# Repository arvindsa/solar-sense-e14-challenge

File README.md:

# SolarSense: Smart Solar Panel Monitoring System

A comprehensive IoT system for real-time solar panel soiling detection using multi-sensor fusion and edge AI. This project monitors three solar panels -one kept clean as a reference baseline to quantify soiling-induced efficiency losses in real time.

**Important: There is an issue with charging circuit. So do not replicate this project unless you know electronics well.**

## Project Overview

SolarSense uses a clean reference panel to cancel out weather effects completely (both panels see the same sky), leaving only soiling-induced losses measurable. The system combines:

- **Hardware**: Custom STM32L476 sensor board with CAN telemetry
- **Gateway**: Arduino UNO Q with dual STM32U585 (bare-metal HAL) and Linux bridge
- **Dashboard**: LabVIEW-based live visualization
- **AI**: Edge Impulse model for clean/alert/soiled classification

**Current Status**: Phase 1 (data collection and live dashboard) complete. Full pipeline implemented but pending end-to-end hardware validation.

Write-up: https://community.element14.com/challenges-projects/design-challenges/on-the-line/b/projects/posts/solarsense---edge-ai-for-optimal-cleaning-of-solar-panels

## Repository Structure

```
firmware/
├── solar-sense-stm32l476/       # Main sensor board (STM32L476RGT6)
├── arduinoq-stm32u585/          # Gateway STM controller (bare-metal HAL)
│   └── bridge/                  # CAN frame bridging logic
└── arduinoq-linux/              # Gateway Linux side (Python bridge)

labview/                         # Dashboard VIs for Window
hardware/                        # PCB schematics and production files
```

Do not use the Python file inside the labview folder. It's only for testing purpose

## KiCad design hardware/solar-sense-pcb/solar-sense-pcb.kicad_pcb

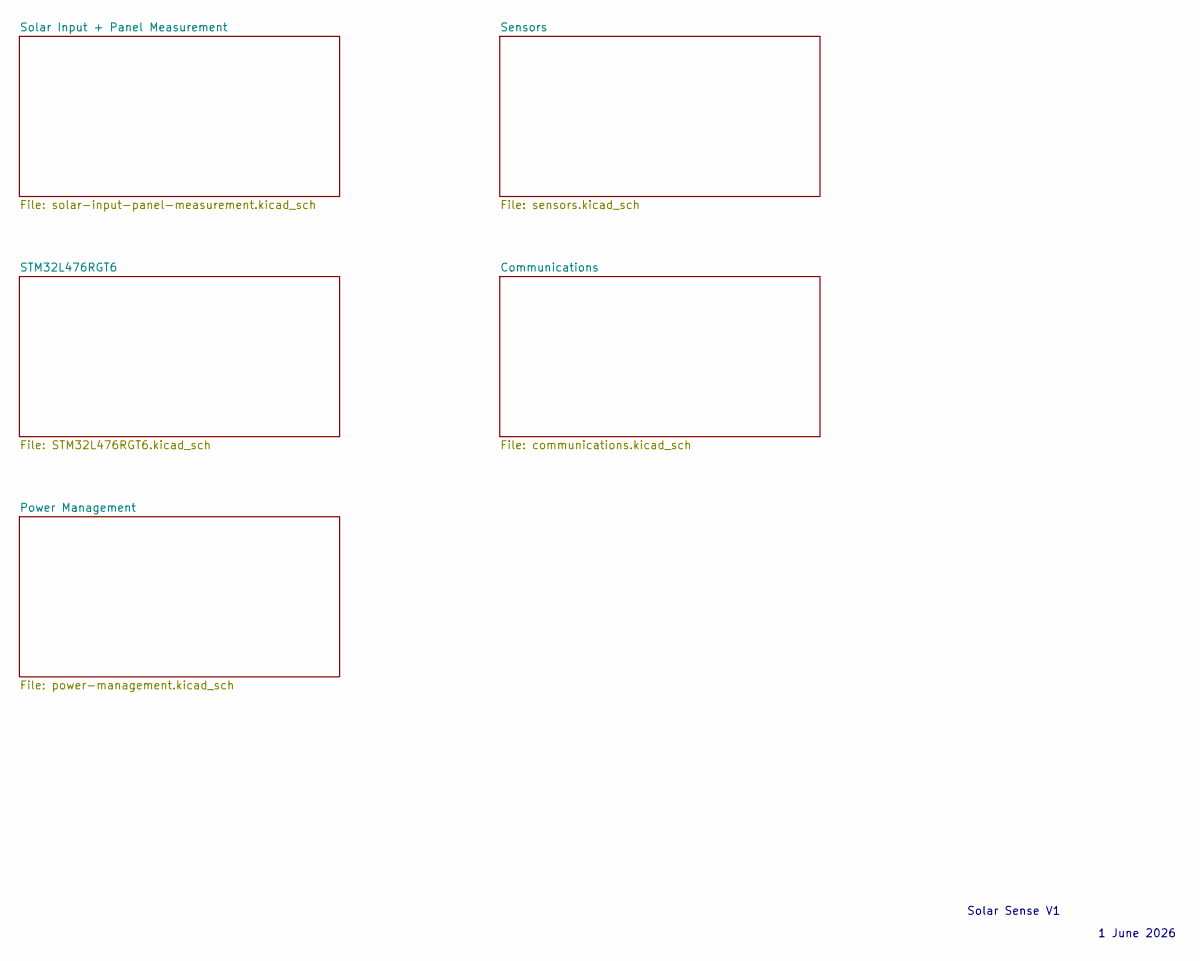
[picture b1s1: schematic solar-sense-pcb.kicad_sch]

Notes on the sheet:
1 June 2026
Solar Sense V1

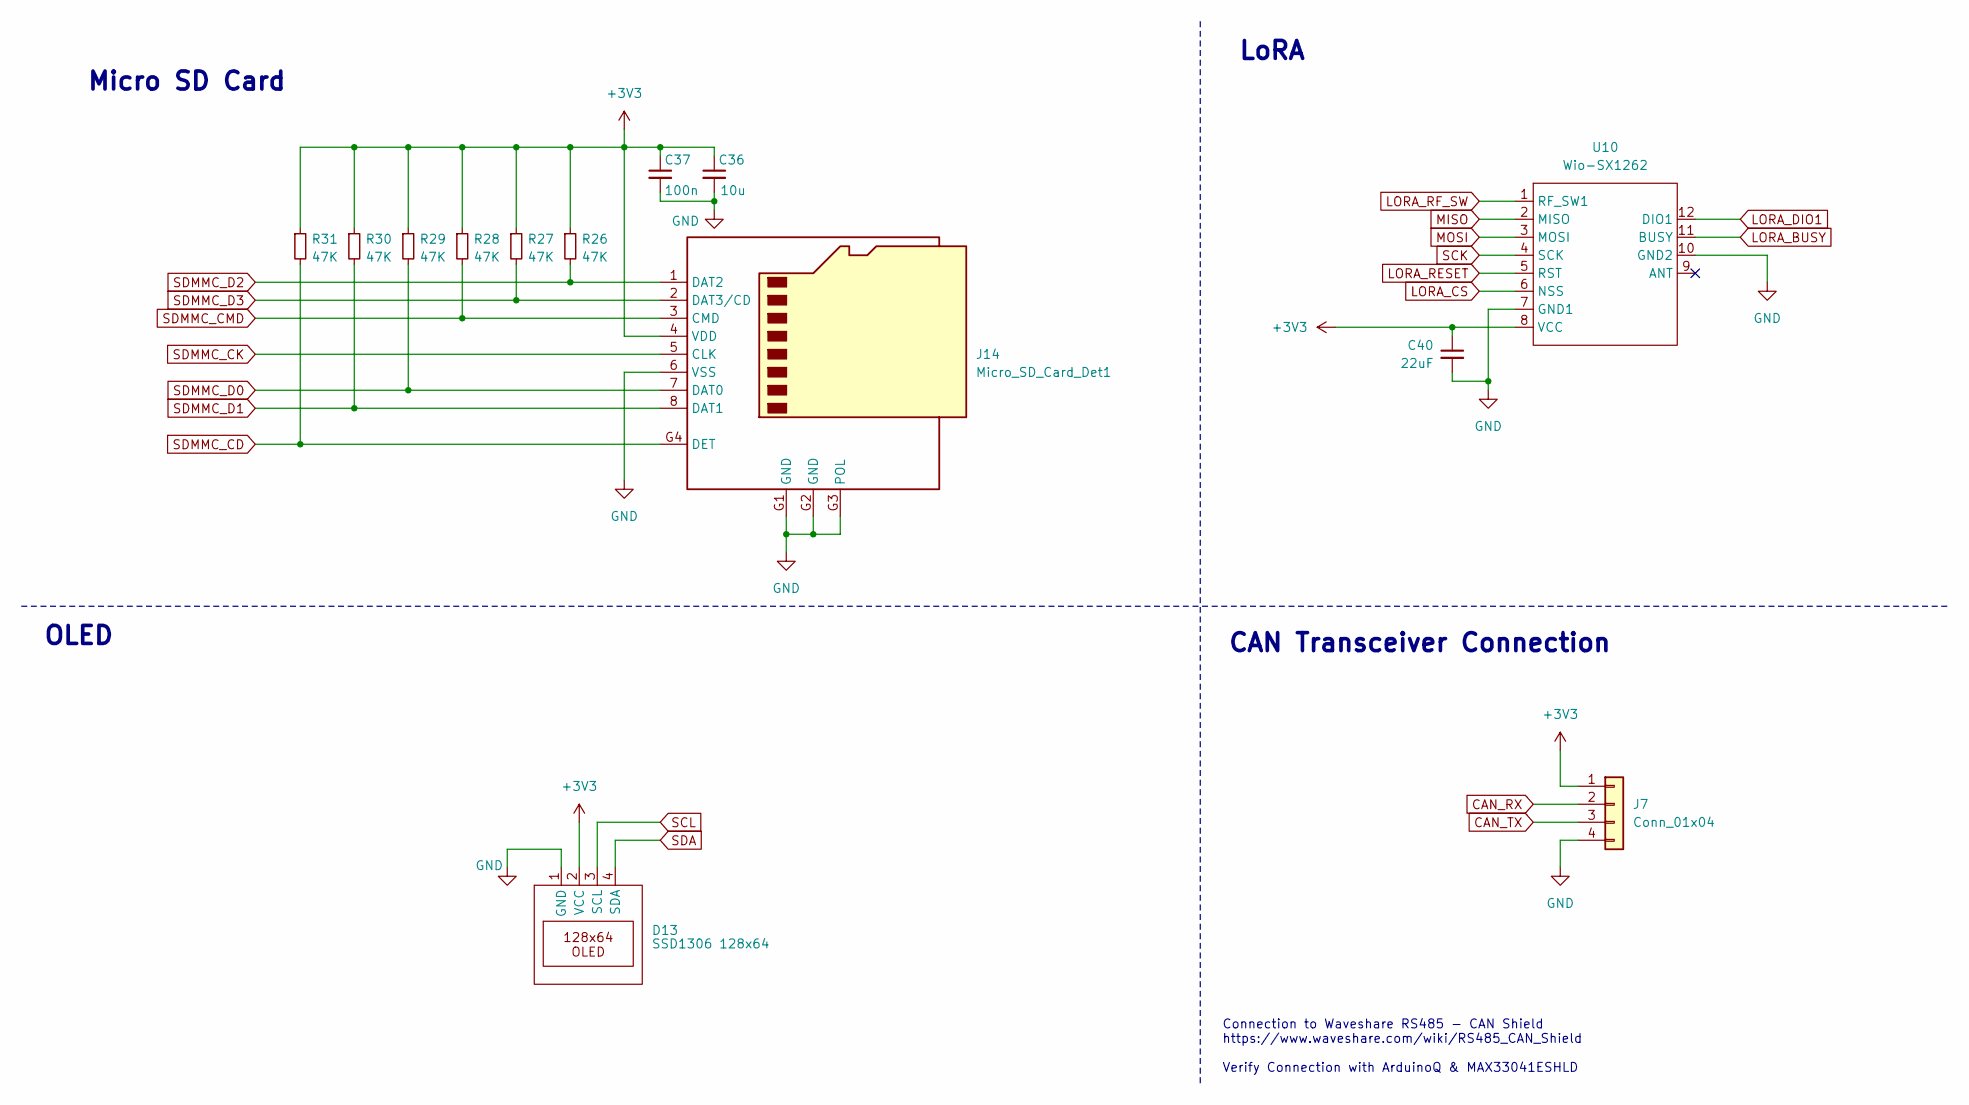
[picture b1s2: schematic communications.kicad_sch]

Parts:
C36: 10u; C_0603_1608Metric_Pad1.08x0.95mm_HandSolder
C37: 100n; C_0603_1608Metric_Pad1.08x0.95mm_HandSolder
C40: 22uF; C_0603_1608Metric
D13: SSD1306 128x64; JST_XH_B4B-XH-A_1x04_P2.50mm_Vertical
J7: Conn_01x04; JST_XH_B4B-XH-A_1x04_P2.50mm_Vertical
J14: Micro_SD_Card_Det1; microSD Molex 47309-2651
R26, R27, R28, R29, R30, R31: 47K; R_0603_1608Metric
U10: Wio-SX1262; Wio-SX1262 PCB Package

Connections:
+3V3: C36.1, C37.1, C40.1, D13.2 (VCC), J7.1, J14.4 (VDD), R26.1, R27.1, R28.1, R29.1, R30.1, R31.1, U10.8 (VCC); also elsewhere on the board
CAN_RX: J7.2; also elsewhere on the board
CAN_TX: J7.3; also elsewhere on the board
GND: C36.2, C37.2, C40.2, D13.1 (GND), J7.4, J14.6 (VSS), J14.G1 (GND), J14.G2 (GND), J14.G3 (POL), U10.7 (GND1), U10.10 (GND2); also elsewhere on the board
LORA_BUSY: U10.11 (BUSY); also elsewhere on the board
LORA_CS: U10.6 (NSS); also elsewhere on the board
LORA_DIO1: U10.12 (DIO1); also elsewhere on the board
LORA_RESET: U10.5 (RST); also elsewhere on the board
LORA_RF_SW: U10.1 (RF_SW1); also elsewhere on the board
MISO: U10.2 (MISO); also elsewhere on the board
MOSI: U10.3 (MOSI); also elsewhere on the board
SCK: U10.4 (SCK); also elsewhere on the board
SCL: D13.3 (SCL); also elsewhere on the board
SDA: D13.4 (SDA); also elsewhere on the board
SDMMC_CD: J14.G4 (DET), R31.2; also elsewhere on the board
SDMMC_CK: J14.5 (CLK); also elsewhere on the board
SDMMC_CMD: J14.3 (CMD), R28.2; also elsewhere on the board
SDMMC_D0: J14.7 (DAT0), R29.2; also elsewhere on the board
SDMMC_D1: J14.8 (DAT1), R30.2; also elsewhere on the board
SDMMC_D2: J14.1 (DAT2), R26.2; also elsewhere on the board
SDMMC_D3: J14.2 (DAT3/CD), R27.2; also elsewhere on the board

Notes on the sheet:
Micro SD Card
CAN Transceiver Connection
Connection to Waveshare RS485 - CAN Shield https://www.waveshare.com/wiki/RS485_CAN_Shield Verify Connection with ArduinoQ & MAX33041ESHLD
LoRA
OLED

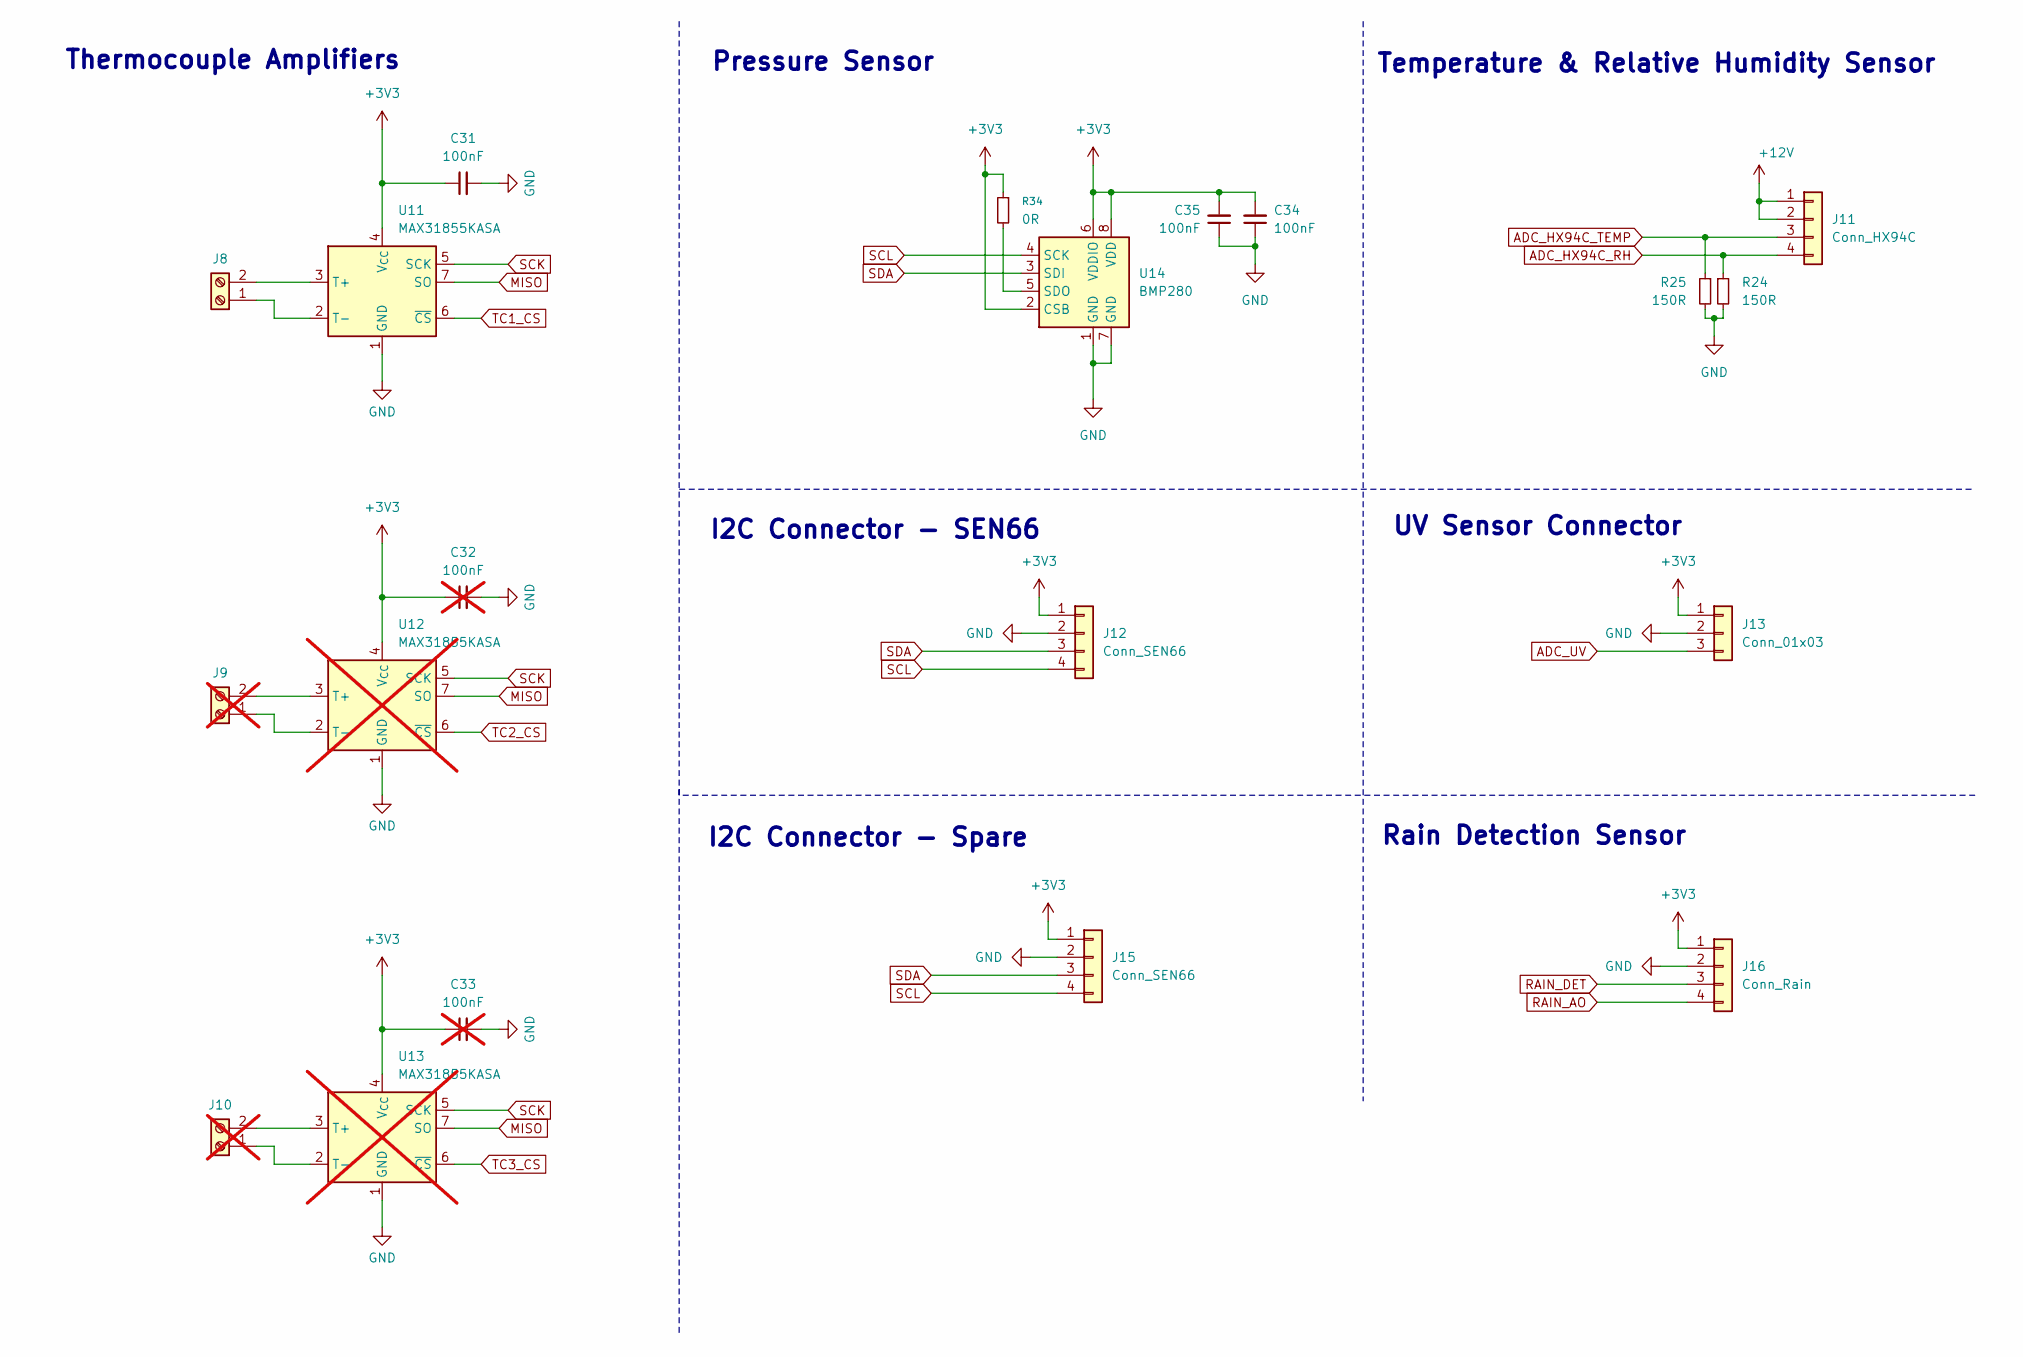
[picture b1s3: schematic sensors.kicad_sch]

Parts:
C31, C34, C35: 100nF; C_0603_1608Metric
C32, C33: 100nF; C_0603_1608Metric; not fitted
J8: Screw_Terminal_01x02; TerminalBlock_4Ucon_1x02_P3.50mm_Vertical
J9, J10: Screw_Terminal_01x02; TerminalBlock_4Ucon_1x02_P3.50mm_Vertical; not fitted
J11: Conn_HX94C; JST_XH_B4B-XH-A_1x04_P2.50mm_Vertical
J12, J15: Conn_SEN66; JST_XH_B4B-XH-A_1x04_P2.50mm_Vertical
J13: Conn_01x03; JST_XH_B3B-XH-A_1x03_P2.50mm_Vertical
J16: Conn_Rain; JST_XH_B4B-XH-A_1x04_P2.50mm_Vertical
R24, R25: 150R; LED_0805_2012Metric
R34: 0R; R_0603_1608Metric
U11: MAX31855KASA; SOIC-8_3.9x4.9mm_P1.27mm
U12, U13: MAX31855KASA; SOIC-8_3.9x4.9mm_P1.27mm; not fitted
U14: BMP280; Bosch_LGA-8_2x2.5mm_P0.65mm_ClockwisePinNumbering

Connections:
+3V3: C31.1, C32.1, C33.1, C34.2, C35.2, J12.1, J13.1, J15.1, J16.1, R34.1, U11.4 (V_{CC}), U12.4 (V_{CC}), U13.4 (V_{CC}), U14.2 (CSB), U14.6 (VDDIO), U14.8 (VDD); also elsewhere on the board
+12V: J11.1, J11.2; also elsewhere on the board
ADC_HX94C_RH: J11.4, R24.1; also elsewhere on the board
ADC_HX94C_TEMP: J11.3, R25.1; also elsewhere on the board
ADC_UV: J13.3; also elsewhere on the board
GND: C31.2, C32.2, C33.2, C34.1, C35.1, J12.2, J13.2, J15.2, J16.2, R24.2, R25.2, U11.1 (GND), U12.1 (GND), U13.1 (GND), U14.1 (GND), U14.7 (GND); also elsewhere on the board
MISO: U11.7 (SO), U12.7 (SO), U13.7 (SO); also elsewhere on the board
unnamed: J8.1, U11.2 (T-)
unnamed: J8.2, U11.3 (T+)
unnamed: J9.1, U12.2 (T-)
unnamed: J9.2, U12.3 (T+)
unnamed: J10.1, U13.2 (T-)
unnamed: J10.2, U13.3 (T+)
unnamed: R34.2, U14.5 (SDO)
RAIN_AO: J16.4; also elsewhere on the board
RAIN_DET: J16.3; also elsewhere on the board
SCK: U11.5 (SCK), U12.5 (SCK), U13.5 (SCK); also elsewhere on the board
SCL: J12.4, J15.4, U14.4 (SCK); also elsewhere on the board
SDA: J12.3, J15.3, U14.3 (SDI); also elsewhere on the board
TC1_CS: U11.6 (~CS); also elsewhere on the board
TC2_CS: U12.6 (~CS); also elsewhere on the board
TC3_CS: U13.6 (~CS); also elsewhere on the board

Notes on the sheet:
I2C Connector - SEN66
I2C Connector - Spare
Pressure Sensor
UV Sensor Connector
Temperature & Relative Humidity Sensor
Thermocouple Amplifiers
Rain Detection Sensor

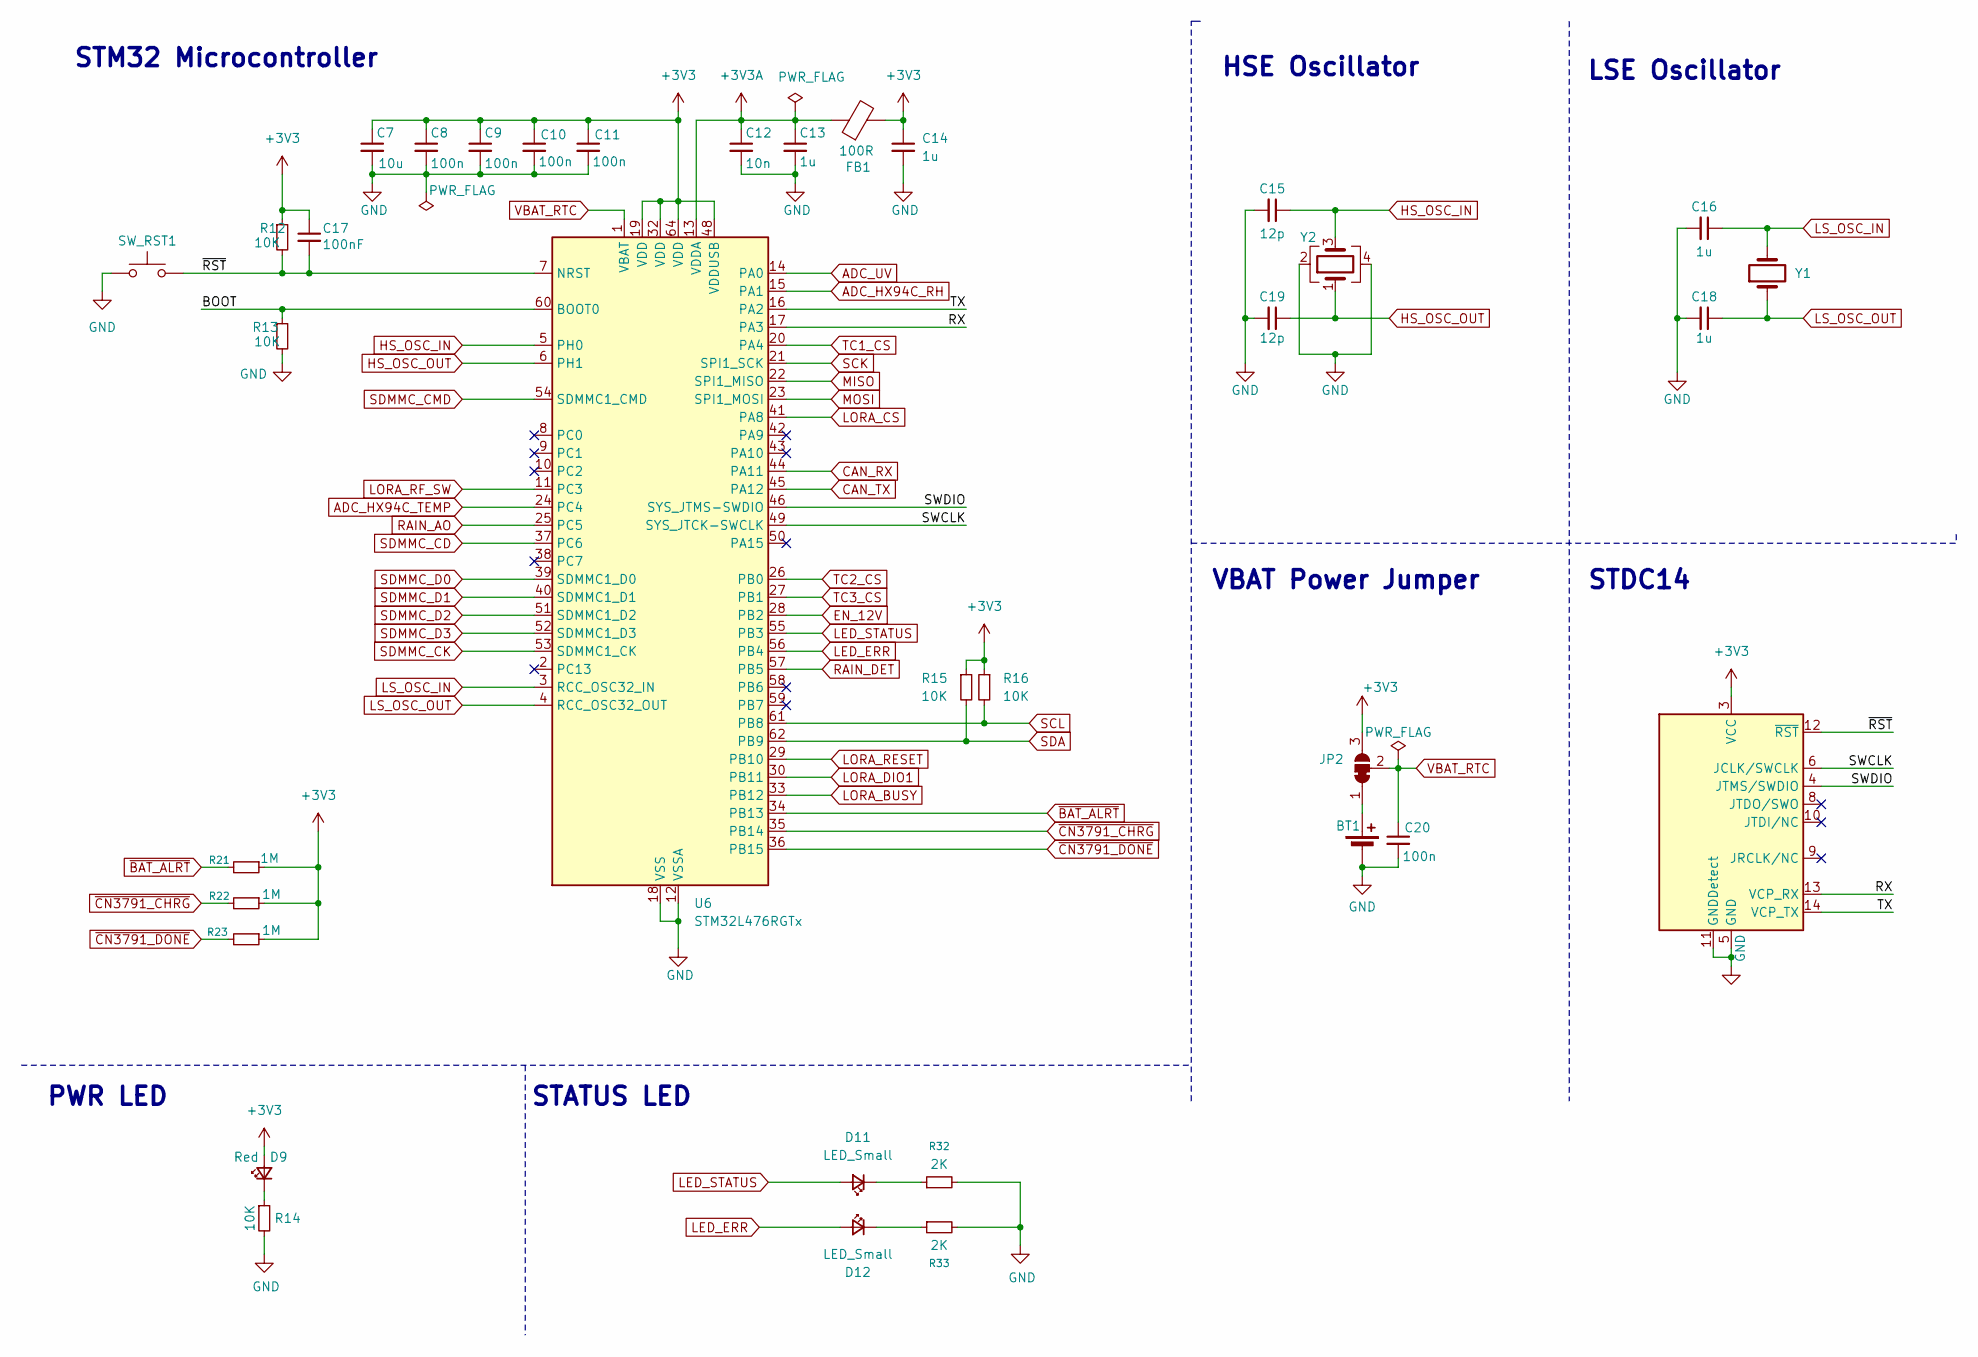
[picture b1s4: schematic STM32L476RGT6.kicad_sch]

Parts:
BT1: Battery_Cell; CH7410-2032LF
C7: 10u; C_0603_1608Metric_Pad1.08x0.95mm_HandSolder
C8, C9, C10, C11, C20: 100n; C_0603_1608Metric_Pad1.08x0.95mm_HandSolder
C12: 10n; C_0603_1608Metric_Pad1.08x0.95mm_HandSolder
C13, C14, C16, C18: 1u; C_0603_1608Metric_Pad1.08x0.95mm_HandSolder
C15, C19: 12p; C_0603_1608Metric_Pad1.08x0.95mm_HandSolder
C17: 100nF; C_0603_1608Metric
D9: Red; LED_0603_1608Metric_Pad1.05x0.95mm_HandSolder
D11, D12: LED_Small; LED_0603_1608Metric
FB1: 100R; R_0603_1608Metric_Pad0.98x0.95mm_HandSolder
J6: Conn_ST_STDC14; PinHeader_2x07_P1.27mm_Vertical_SMD
JP2: SolderJumper_3_Bridged12; SolderJumper-3_P1.3mm_Bridged12_RoundedPad1.0x1.5mm
R12, R13, R15, R16: 10K; R_0603_1608Metric
R14: 10K; R_0603_1608Metric_Pad0.98x0.95mm_HandSolder
R21, R22, R23: 1M; R_0603_1608Metric
R32, R33: 2K; R_0603_1608Metric
SW_RST1: SW_Push; SW_Tactile_SPST_NO_Straight_CK_PTS636Sx25SMTRLFS
U6: STM32L476RGTx; LQFP-64_10x10mm_P0.5mm
Y1: CM7V-T1A-32.768kHz-9pF-20PPM-TA-QC; Crystal_SMD_3215-2Pin_3.2x1.5mm
Y2: 7M-16.000MAAJ-T; Crystal_SMD_TXC_7M-4Pin_3.2x2.5mm

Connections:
+3V3: C7.1, C8.1, C9.1, C10.1, C11.1, C14.1, C17.1, D9.2 (A), FB1.2, J6.3 (VCC), JP2.3 (B), R12.1, R15.1, R16.1, R21.1, R22.1, R23.1, U6.19 (VDD), U6.32 (VDD), U6.48 (VDDUSB), U6.64 (VDD); also elsewhere on the board
+3V3A: C12.1, C13.1, FB1.1, U6.13 (VDDA)
/STM32L476RGT6/BOOT: R13.1, U6.60 (BOOT0)
/STM32L476RGT6/RX: J6.13 (VCP_RX), U6.17 (PA3)
/STM32L476RGT6/SWCLK: J6.6 (JCLK/SWCLK), U6.49 (SYS_JTCK-SWCLK)
/STM32L476RGT6/SWDIO: J6.4 (JTMS/SWDIO), U6.46 (SYS_JTMS-SWDIO)
/STM32L476RGT6/TX: J6.14 (VCP_TX), U6.16 (PA2)
/STM32L476RGT6/~RST: C17.2, J6.12 (~RST), R12.2, SW_RST1.2, U6.7 (NRST)
ADC_HX94C_RH: U6.15 (PA1); also elsewhere on the board
ADC_HX94C_TEMP: U6.24 (PC4); also elsewhere on the board
ADC_UV: U6.14 (PA0); also elsewhere on the board
CAN_RX: U6.44 (PA11); also elsewhere on the board
CAN_TX: U6.45 (PA12); also elsewhere on the board
EN_12V: U6.28 (PB2); also elsewhere on the board
GND: BT1.2 (-), C7.2, C8.2, C9.2, C10.2, C11.2, C12.2, C13.2, C14.2, C15.2, C16.2, C18.2, C19.2, C20.2, J6.5 (GND), J6.7 (GND), J6.11 (GNDDetect), R13.2, R14.2, R32.2, R33.2, SW_RST1.1, U6.12 (VSSA), U6.18 (VSS), U6.31 (VSS), U6.47 (VSS), U6.63 (VSS), Y2.2, Y2.4; also elsewhere on the board
HS_OSC_IN: C15.1, U6.5 (PH0), Y2.3
HS_OSC_OUT: C19.1, U6.6 (PH1), Y2.1
LED_ERR: D12.2 (A), U6.56 (PB4)
LED_STATUS: D11.2 (A), U6.55 (PB3)
LORA_BUSY: U6.33 (PB12); also elsewhere on the board
LORA_CS: U6.41 (PA8); also elsewhere on the board
LORA_DIO1: U6.30 (PB11); also elsewhere on the board
LORA_RESET: U6.29 (PB10); also elsewhere on the board
LORA_RF_SW: U6.11 (PC3); also elsewhere on the board
LS_OSC_IN: C16.1, U6.3 (RCC_OSC32_IN), Y1.2
LS_OSC_OUT: C18.1, U6.4 (RCC_OSC32_OUT), Y1.1
MISO: U6.22 (SPI1_MISO); also elsewhere on the board
MOSI: U6.23 (SPI1_MOSI); also elsewhere on the board
unnamed: BT1.1 (+), JP2.1 (A)
unnamed: D9.1 (K), R14.1
unnamed: D11.1 (K), R32.1
unnamed: D12.1 (K), R33.1
RAIN_AO: U6.25 (PC5); also elsewhere on the board
RAIN_DET: U6.57 (PB5); also elsewhere on the board
SCK: U6.21 (SPI1_SCK); also elsewhere on the board
SCL: R16.2, U6.61 (PB8); also elsewhere on the board
SDA: R15.2, U6.62 (PB9); also elsewhere on the board
SDMMC_CD: U6.37 (PC6); also elsewhere on the board
SDMMC_CK: U6.53 (SDMMC1_CK); also elsewhere on the board
SDMMC_CMD: U6.54 (SDMMC1_CMD); also elsewhere on the board
SDMMC_D0: U6.39 (SDMMC1_D0); also elsewhere on the board
SDMMC_D1: U6.40 (SDMMC1_D1); also elsewhere on the board
SDMMC_D2: U6.51 (SDMMC1_D2); also elsewhere on the board
SDMMC_D3: U6.52 (SDMMC1_D3); also elsewhere on the board
TC1_CS: U6.20 (PA4); also elsewhere on the board
TC2_CS: U6.26 (PB0); also elsewhere on the board
TC3_CS: U6.27 (PB1); also elsewhere on the board
VBAT_RTC: C20.1, JP2.2 (C), U6.1 (VBAT)
~BAT_ALRT: R21.2, U6.34 (PB13); also elsewhere on the board
~CN3791_CHRG: R22.2, U6.35 (PB14); also elsewhere on the board
~CN3791_DONE: R23.2, U6.36 (PB15); also elsewhere on the board

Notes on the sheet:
LSE Oscillator
VBAT Power Jumper
STM32 Microcontroller
PWR LED
STATUS LED
HSE Oscillator
STDC14

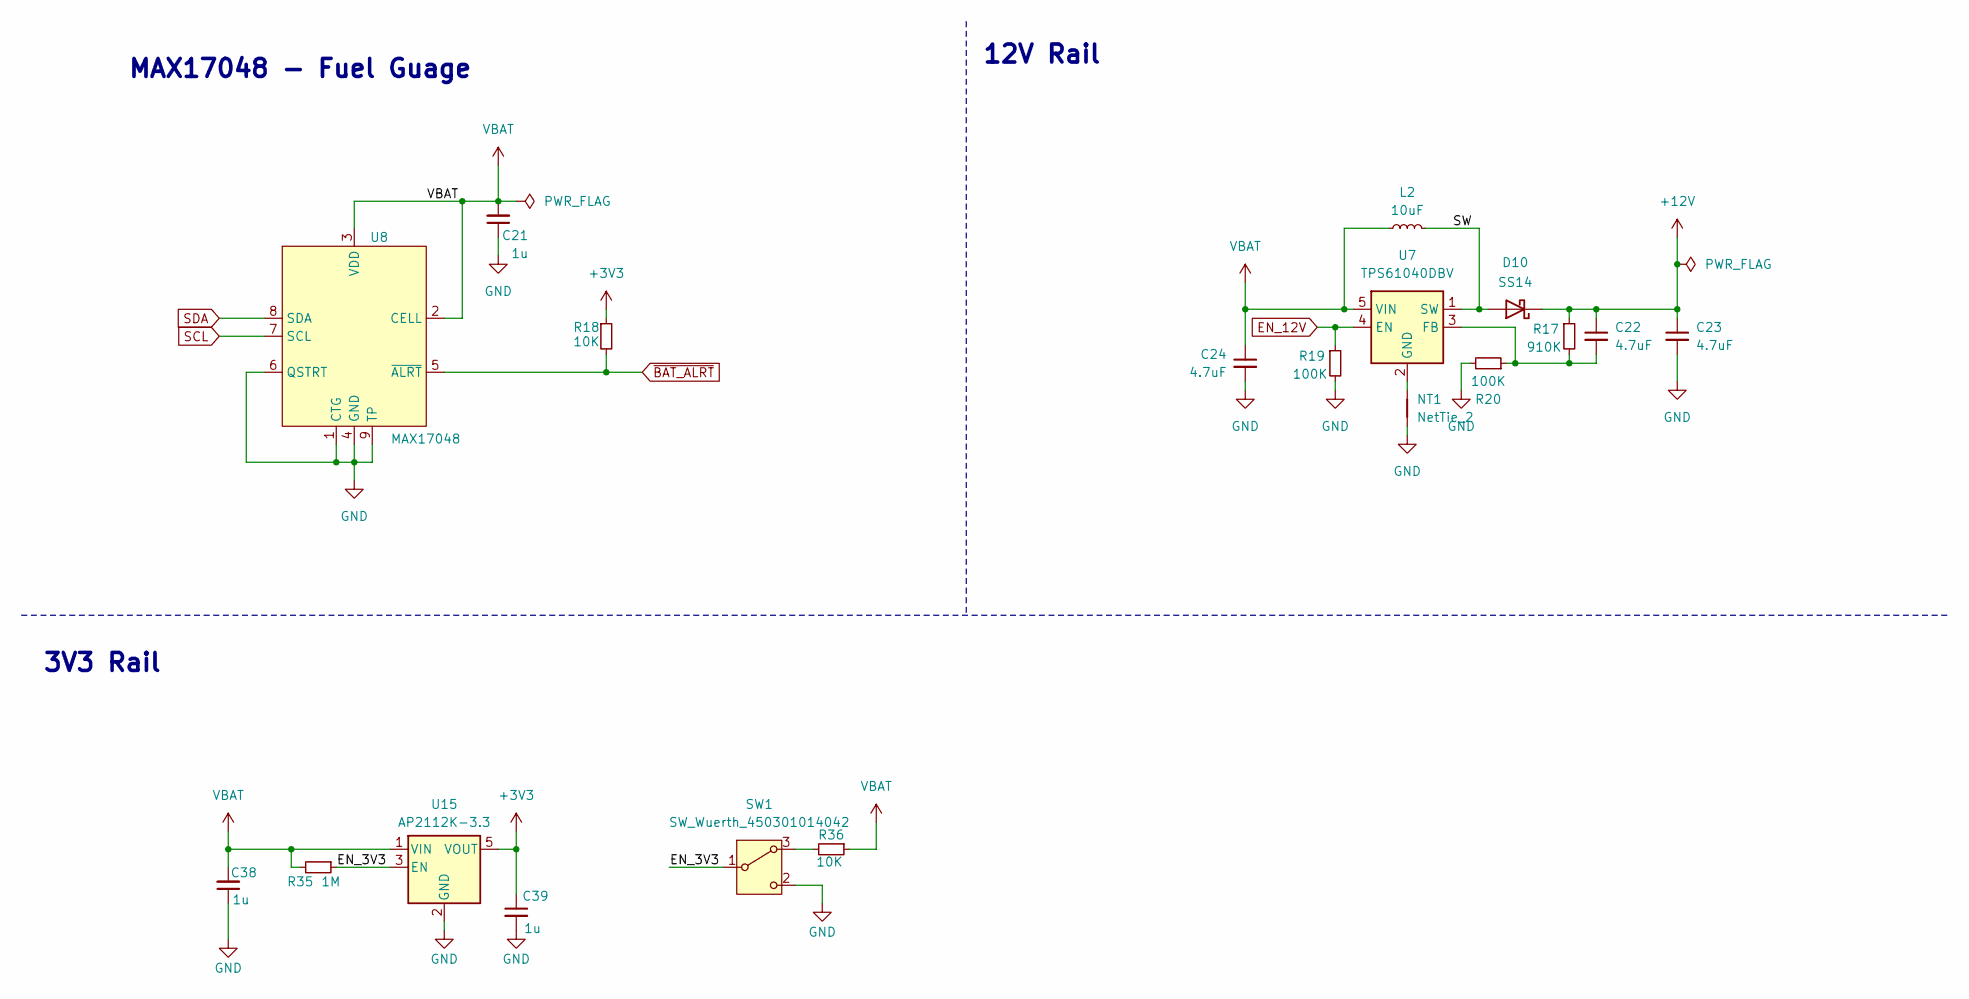
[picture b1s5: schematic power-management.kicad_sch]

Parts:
C21: 1u; C_0603_1608Metric_Pad1.08x0.95mm_HandSolder
C22, C23, C24: 4.7uF; C_0603_1608Metric
C38, C39: 1u; C_0603_1608Metric
D10: SS14; D_SMA
L2: 10uF; L_TDK_VLS6045EX_VLS6045AF
NT1: NetTie_2; NetTie-2_SMD_Pad0.5mm
R17: 910K; R_0603_1608Metric
R18: 10K; R_0603_1608Metric_Pad0.98x0.95mm_HandSolder
R19, R20: 100K; R_0603_1608Metric
R35: 1M; R_0603_1608Metric
R36: 10K; R_0603_1608Metric
SW1: SW_Wuerth_450301014042; Weurth 450302014072 - Overhang
U7: TPS61040DBV; SOT-23-5
U8: MAX17048; MAX17048G+T10
U15: AP2112K-3.3; SOT-23-5

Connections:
+3V3: C39.1, R18.1, U15.5 (VOUT); also elsewhere on the board
+12V: C22.1, C23.1, D10.1 (K), R17.1; also elsewhere on the board
/Power Management/EN_3V3: R35.1, SW1.1 (B), U15.3 (EN)
/Power Management/SW: D10.2 (A), L2.2, U7.1 (SW)
EN_12V: R19.1, U7.4 (EN); also elsewhere on the board
GND: C21.1, C23.2, C24.2, C38.1, C39.2, NT1.1, R19.2, R20.2, SW1.2 (C), U8.1 (CTG), U8.4 (GND), U8.6 (QSTRT), U8.9 (TP), U15.2 (GND); also elsewhere on the board
unnamed: R36.2, SW1.3 (A)
unnamed: C22.2, R17.2, R20.1, U7.3 (FB)
unnamed: NT1.2, U7.2 (GND)
SCL: U8.7 (SCL); also elsewhere on the board
SDA: U8.8 (SDA); also elsewhere on the board
VBAT: C21.2, C24.1, C38.2, L2.1, R35.2, R36.1, U7.5 (VIN), U8.2 (CELL), U8.3 (VDD), U15.1 (VIN); also elsewhere on the board
~BAT_ALRT: R18.2, U8.5 (~ALRT); also elsewhere on the board

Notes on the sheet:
12V Rail
MAX17048 - Fuel Guage
3V3 Rail

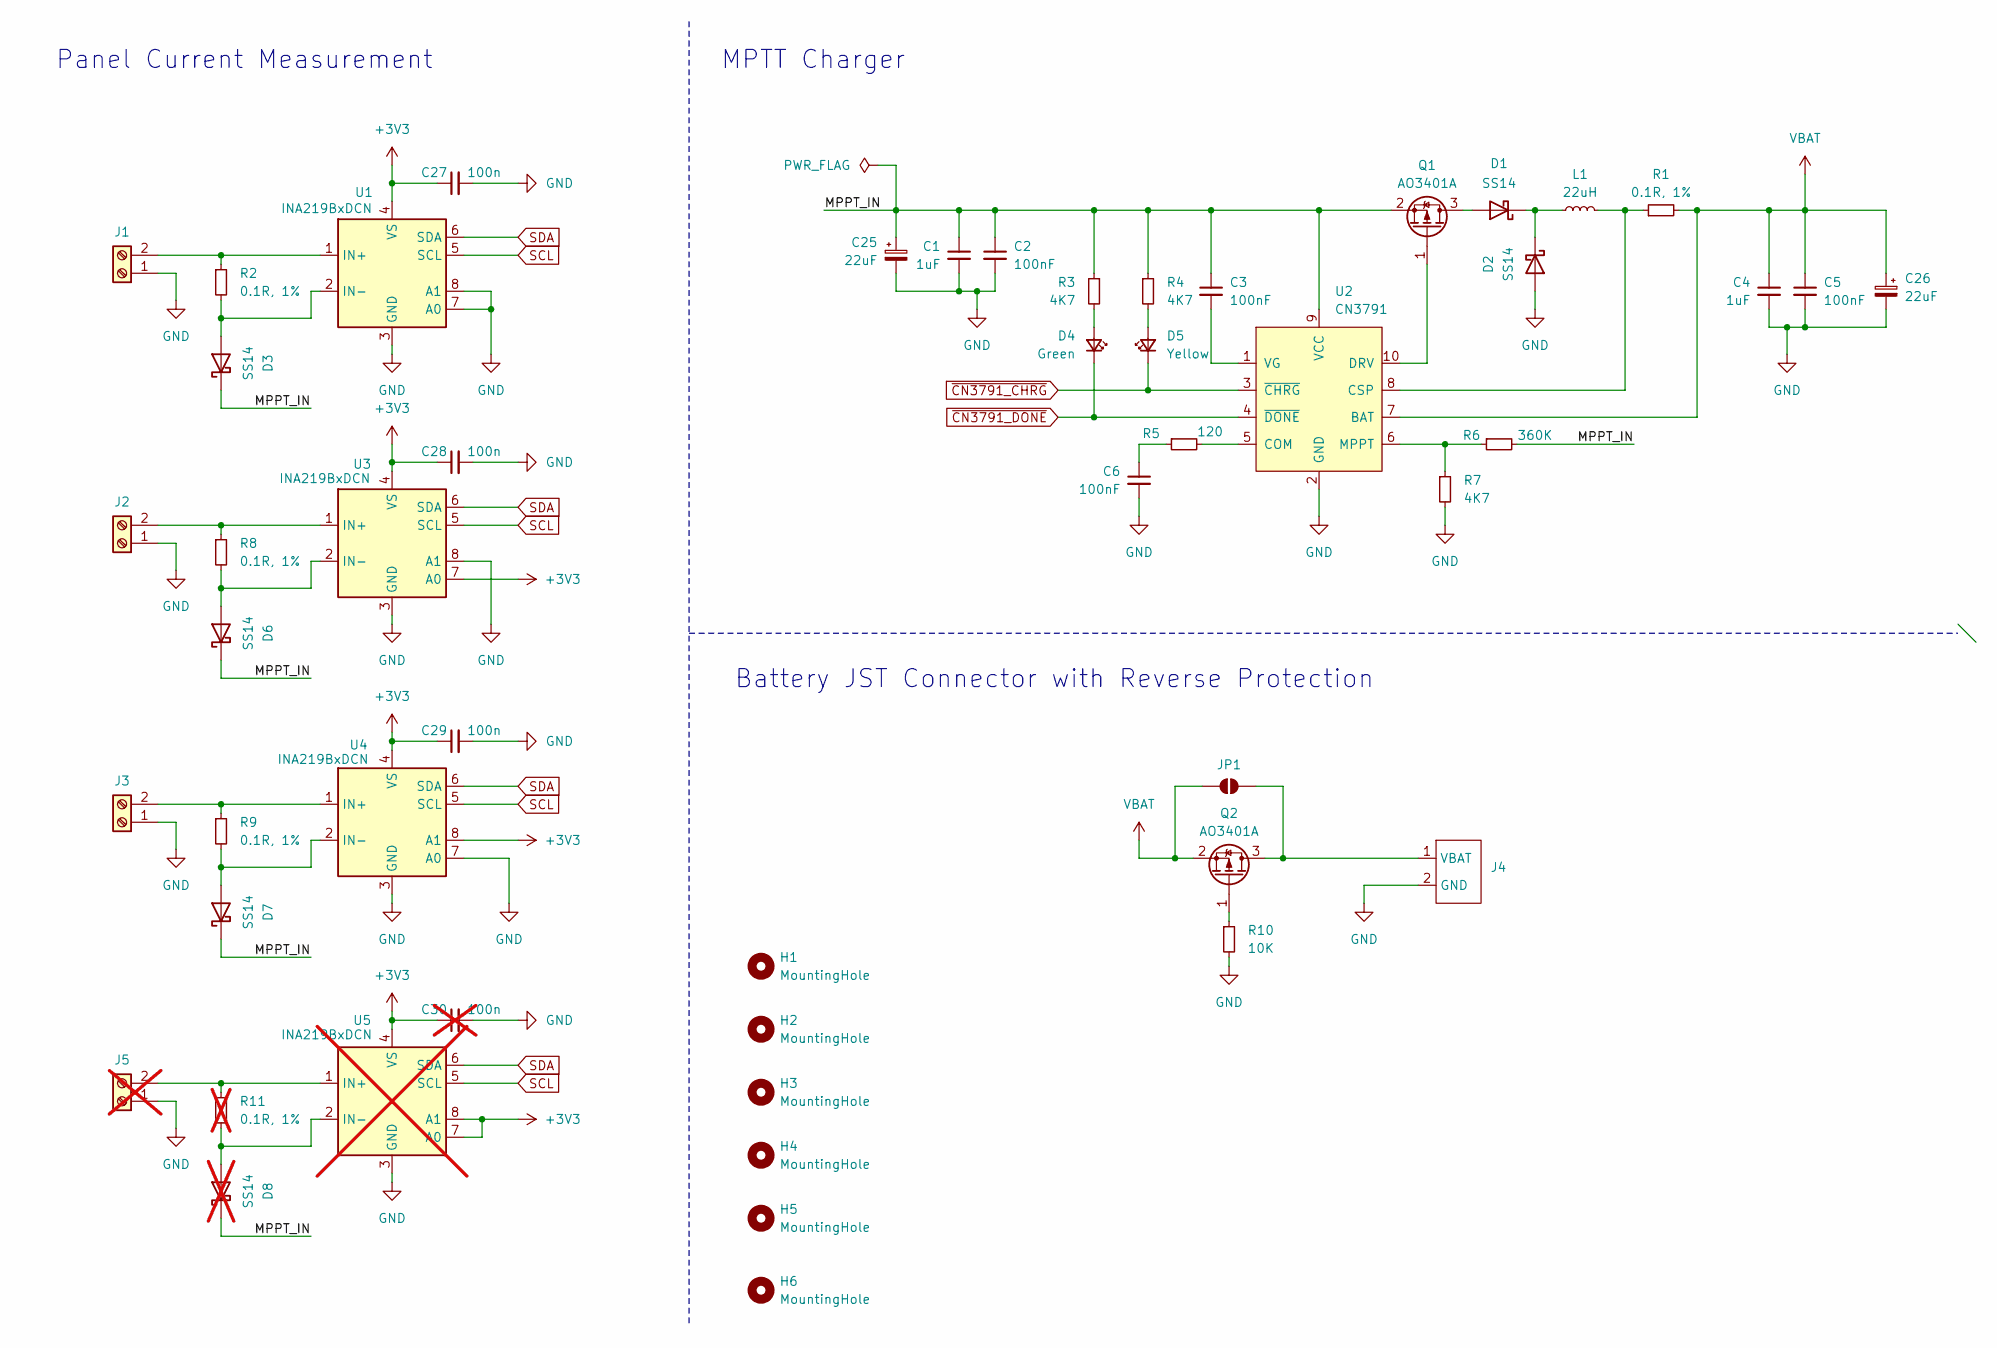
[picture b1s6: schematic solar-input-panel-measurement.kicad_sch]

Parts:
C1, C4: 1uF; C_0603_1608Metric
C2, C3, C5, C6: 100nF; C_0603_1608Metric
C25, C26: 22uF; CP_Elec_5x5.3
C27, C28, C29: 100n; C_0603_1608Metric_Pad1.08x0.95mm_HandSolder
C30: 100n; C_0603_1608Metric_Pad1.08x0.95mm_HandSolder; not fitted
D1, D2, D3, D6, D7: SS14; D_SMA
D4: Green; LED_0603_1608Metric
D5: Yellow; LED_0603_1608Metric
D8: SS14; D_SMA; not fitted
H1, H2, H3, H4, H5, H6: MountingHole; MountingHole_3.2mm_M3
J1, J2, J3: Screw_Terminal_01x02; TerminalBlock_4Ucon_1x02_P3.50mm_Vertical
J4: JST_PH_S2B-PH-SM4-TB_1x02-1MP_P2.00mm_Horizontal
J5: Screw_Terminal_01x02; TerminalBlock_4Ucon_1x02_P3.50mm_Vertical; not fitted
JP1: SolderJumper_2_Open; SolderJumper-2_P1.3mm_Open_RoundedPad1.0x1.5mm
L1: 22uH; L_Sunlord_SWPA8040S
Q1, Q2: AO3401A; SOT-23
R1: 0.1R, 1%; R_1210_3225Metric
R2, R8, R9: 0.1R, 1%; R_2512_6332Metric
R3, R4, R7: 4K7; R_0603_1608Metric
R5: 120; R_0603_1608Metric
R6: 360K; R_0603_1608Metric
R10: 10K; R_0603_1608Metric
R11: 0.1R, 1%; R_2512_6332Metric; not fitted
U1, U3, U4: INA219BxDCN; SOT-23-8
U2: CN3791; SSOP-10-1EP_3.9x4.9mm_P1mm_EP2.1x3.3mm_ThermalVias
U5: INA219BxDCN; SOT-23-8; not fitted

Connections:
+3V3: C27.1, C28.1, C29.1, C30.1, U1.4 (VS), U3.4 (VS), U3.7 (A0), U4.4 (VS), U4.8 (A1), U5.4 (VS), U5.7 (A0), U5.8 (A1); also elsewhere on the board
/Solar Input + Panel Measurement/MPPT_IN: C1.1, C2.1, C3.1, C25.1, D3.1 (K), D6.1 (K), D7.1 (K), D8.1 (K), Q1.2 (S), R3.1, R4.1, R6.2, U2.9 (VCC)
GND: C1.2, C2.2, C4.2, C5.2, C6.2, C25.2, C26.2, C27.2, C28.2, C29.2, C30.2, D2.2 (A), J1.1, J2.1, J3.1, J4.2 (GND), J5.1, R7.2, R10.2, U1.3 (GND), U1.7 (A0), U1.8 (A1), U2.2 (GND), U3.3 (GND), U3.8 (A1), U4.3 (GND), U4.7 (A0), U5.3 (GND); also elsewhere on the board
unnamed: C6.1, R5.1
unnamed: D1.2 (A), Q1.3 (D)
unnamed: D1.1 (K), D2.1 (K), L1.1
unnamed: D3.2 (A), R2.2, U1.2 (IN-)
unnamed: D4.2 (A), R3.2
unnamed: D5.2 (A), R4.2
unnamed: D6.2 (A), R8.2, U3.2 (IN-)
unnamed: D7.2 (A), R9.2, U4.2 (IN-)
unnamed: D8.2 (A), R11.2, U5.2 (IN-)
unnamed: J1.2, R2.1, U1.1 (IN+)
unnamed: J2.2, R8.1, U3.1 (IN+)
unnamed: J3.2, R9.1, U4.1 (IN+)
unnamed: J4.1 (VBAT), JP1.2 (B), Q2.3 (D)
unnamed: J5.2, R11.1, U5.1 (IN+)
unnamed: Q1.1 (G), U2.10 (DRV)
unnamed: Q2.1 (G), R10.1
unnamed: R5.2, U2.5 (COM)
unnamed: L1.2, R1.1, U2.8 (CSP)
unnamed: R6.1, R7.1, U2.6 (MPPT)
unnamed: C3.2, U2.1 (VG)
SCL: U1.5 (SCL), U3.5 (SCL), U4.5 (SCL), U5.5 (SCL); also elsewhere on the board
SDA: U1.6 (SDA), U3.6 (SDA), U4.6 (SDA), U5.6 (SDA); also elsewhere on the board
VBAT: C4.1, C5.1, C26.1, JP1.1 (A), Q2.2 (S), R1.2, U2.7 (BAT); also elsewhere on the board
~CN3791_CHRG: D5.1 (K), U2.3 (~CHRG); also elsewhere on the board
~CN3791_DONE: D4.1 (K), U2.4 (~DONE); also elsewhere on the board

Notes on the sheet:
MPTT Charger
Battery JST Connector with Reverse Protection
Panel Current Measurement
